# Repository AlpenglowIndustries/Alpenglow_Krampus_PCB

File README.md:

# Alpenglow_Krampus_PCB
Kicad files for Merry Krampus PCB including schematic and assembly pdfs.

Merry Krampus is available on our website and Tindie, in an assembled version, Hacker Challenge version, and Just the Board version.
https://www.alpenglowindustries.com/store/p23/krampus.html#/
https://www.tindie.com/products/alpenglow/merry-krampus/

Instructions:
https://www.alpenglowindustries.com/krampus

## Notes for Next Revision
1. add series programming resistors
2. change 10k to 100k
3. add polarity mark to programming conn
4. make programming conn pattern bigger
5. add text to switches

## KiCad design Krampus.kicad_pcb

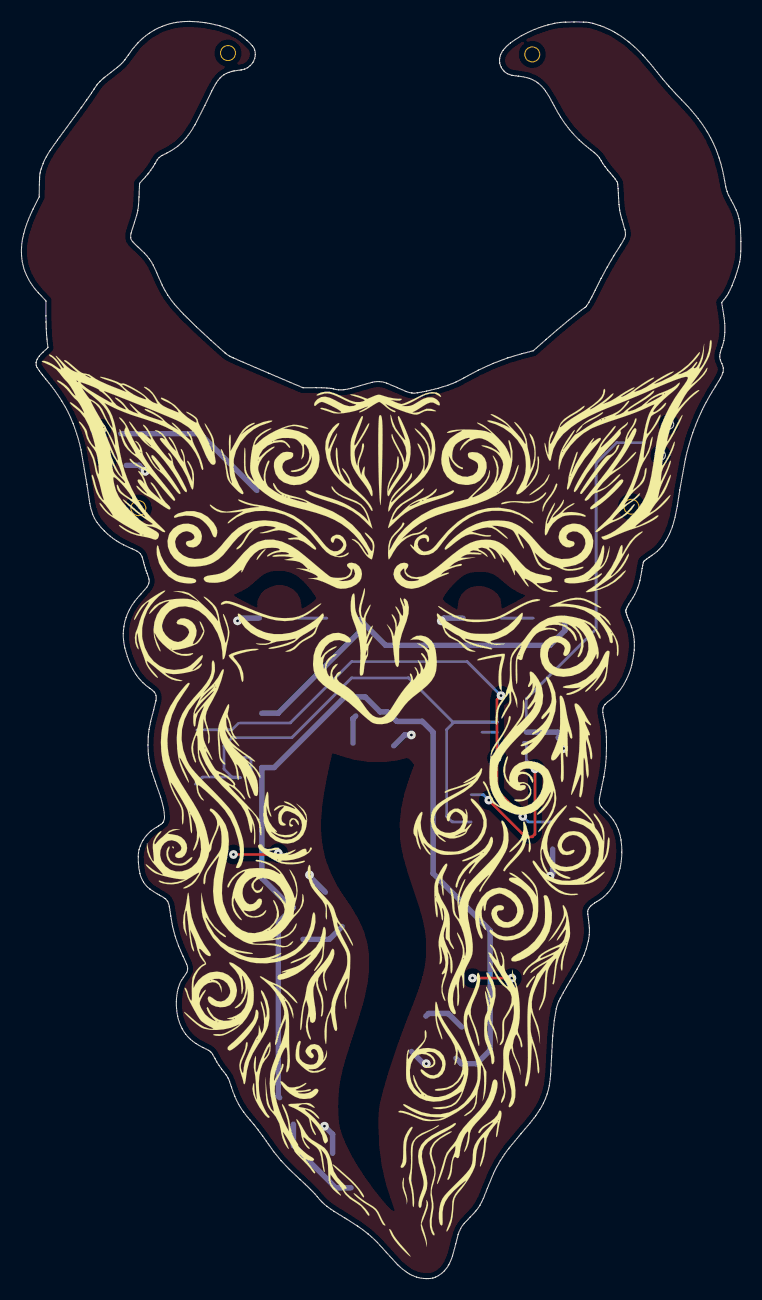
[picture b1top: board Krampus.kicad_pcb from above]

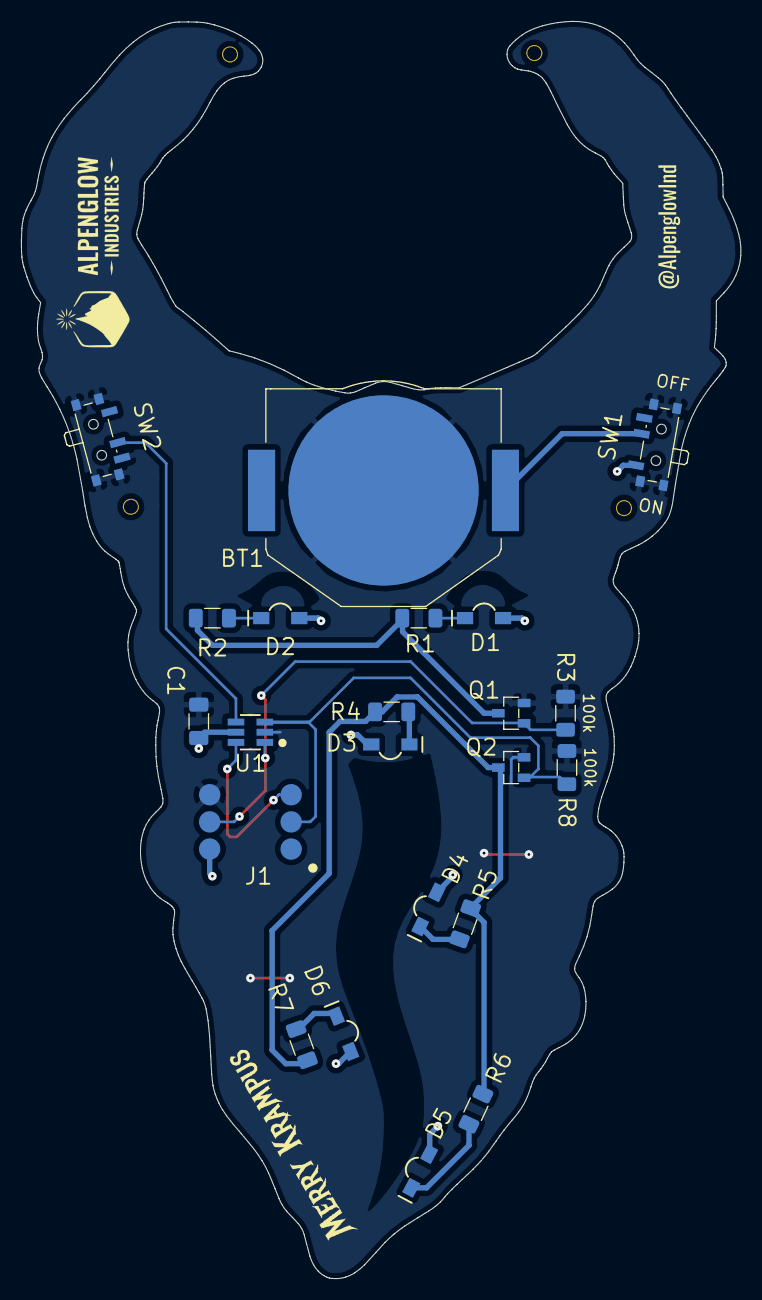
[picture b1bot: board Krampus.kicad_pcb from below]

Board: 2 copper layers, 67.3 x 117.5 mm, 27 parts (23 on the bottom side), 15 nets.

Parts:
BT1: Battery_Cell; BatteryHolder_CR2032_SMT
C1: 0.1; C_1206_3216Metric_Pad1.33x1.80mm_HandSolder
D1, D2, D3, D4, D5, D6: LED; LED_1204_RTA_2P
G2: LOGO; Red
G3: LOGO; Red-back
G4: LOGO; WhitenoMouth
G5: LOGO; GoldwithTeeth
G6: LOGO; Alpenglow_Logo_Horiz_8mm
J1: AVR-ISP-6; CONN-ISP-POGO-SMT
Q1, Q2: Q_NMOS_GSD; SOT-23-3
R1, R2, R4, R5, R6, R7: 470; R_1206_3216Metric_Pad1.30x1.75mm_HandSolder
R3, R8: 100k; R_1206_3216Metric_Pad1.30x1.75mm_HandSolder
SW1: SW_SPDT_Flipped; SW_SPDT_PCM12
SW2: SW_SPDT; SW_SPDT_PCM12
U1: ATtiny4-TS-PROG; SOT-23-6_Handsoldering

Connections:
+V: C1.1, D1.2, D2.2, D3.2, D4.2, D5.2, D6.2, J1.2, SW1.1, U1.5
/EYES: Q1.3, R1.2, R2.2
/PB0: J1.4, Q1.1, R3.1, U1.1
/PB1: J1.3, Q2.1, R8.1, U1.3
/PB2: SW2.2, U1.4
/RESET: J1.5, U1.6
/TONGUE: Q2.3, R4.2, R5.2, R6.2, R7.2
GND: BT1.2, C1.2, J1.6, Q1.2, Q2.2, R3.2, R8.2, SW2.3, U1.2
unnamed: BT1.1, SW1.2
unnamed: D1.1, R1.1
unnamed: D2.1, R2.1
unnamed: D3.1, R4.1
unnamed: D4.1, R5.1
unnamed: D5.1, R6.1
unnamed: D6.1, R7.1

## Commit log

2021-11-08 Initial layout, traces routed but planes not poured yet.
2021-11-09 Added copper pours and keepout areas for tongue and eyes. Everything done except edge cuts and revised mouth (want it to be gold)
2021-11-11 Added board outline, Changed teeth to gold, other tweaks and adjustments to layout
2021-11-13 generated gerbers, other fab files, and BOM
2021-11-18 deleted old export
2021-12-21 updated sch for final values, added pdfs for schematic and assembly, updated readme for next version notes, added template to schematic, added BOM
2021-12-21 moved gerbers into a folder for better clarity
2022-09-15 Updated board name with font, updated @alpenglowind to oswald font
2022-10-14 Changed 10k resistor value to 100k
2022-10-14 Added On OFF labels and pin1 mark on back silkscreen
2022-10-26 Assembly drawings, Schematic
2022-10-26 Added title block, updated schematic PDF
2022-10-27 updated BOM
2022-10-27 Changed BOM to CSV file
2022-10-27 Updated gitignore, changed BOM to CSV file
2026-01-06 added Krampus artwork files
